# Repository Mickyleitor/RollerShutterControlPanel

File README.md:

# Roller Shutter Control Panel

Embedded wall panel for motorized shutters over radio; with LCD; buttons; Wi-Fi via ESP8266; clock;
and temperature. Open hardware with 3D-printed parts; off-the-shelf modules; and a PCB using an
ATMega328P plus ESP8266.

## Motivation and origins

Built to stop sunrise from waking me early; first a simple wall controller; then my 2020 Bachelor’s
thesis; now an open build others can replicate; learn from; and adapt. Also a testbed for new ideas.

## Project status; what it does today

Actively used and stable. Local controller for **three** shutters; buttons to move; LCD for time and
date; current temperature from the internet; on-device Wi-Fi setup; ESP8266 firmware updates over
the air. No cloud required.

## Current functionality

- **Three shutters**; Left; Center; Right; actions: Up; Down; Stop at any time.
- **16×2 I²C LCD**; Shutter management, clock on idle and configuration menu.
- **Current temperature**; periodic OpenWeatherMap request; hides value when unavailable.
- **On-device Wi-Fi setup**; scan networks; choose SSID; enable or disable Wi-Fi and OTA;
- **Auto reconnect**; for both wifi attemps and weather requests.
- **Time and timezone editor**; set time and timezone.
- **OTA updates** for the ESP8266 using ArduinoOTA; handled in the background.
- **Buzzer feedback**; adjustable volume; enable or disable; accept and error tones.
- **Debug pages**; soft reset counter; current SSID with link status; device IP.

## Repository layout

```
Docs/                     Documents
├─ Figures/               Diagrams, schematics, screenshots
├─ Files/                 Raw docs (.docx, .pdf, etc.)
└─ Photos/                Prototyping photos

Firmware_Arduino/         Arduino MCU source
Firmware_ESP8266/         ESP8266 source
Firmware_Processing_HCI/  Processing-IDE files

PCB_Design/               KiCAD board files
├─ Libraries/             Custom symbols
└─ Modules/               Footprints & 3D models

3D_Design/                Panel case models
```

## Tools

Free or evaluation to avoid licensing issues:  
• KiCAD; Arduino IDE; Google SketchUp (free); GIMP; Cameo Systems Modeler (evaluation);  
  draw.io (online); VSCode.

## License

CERN Open Hardware Licence.

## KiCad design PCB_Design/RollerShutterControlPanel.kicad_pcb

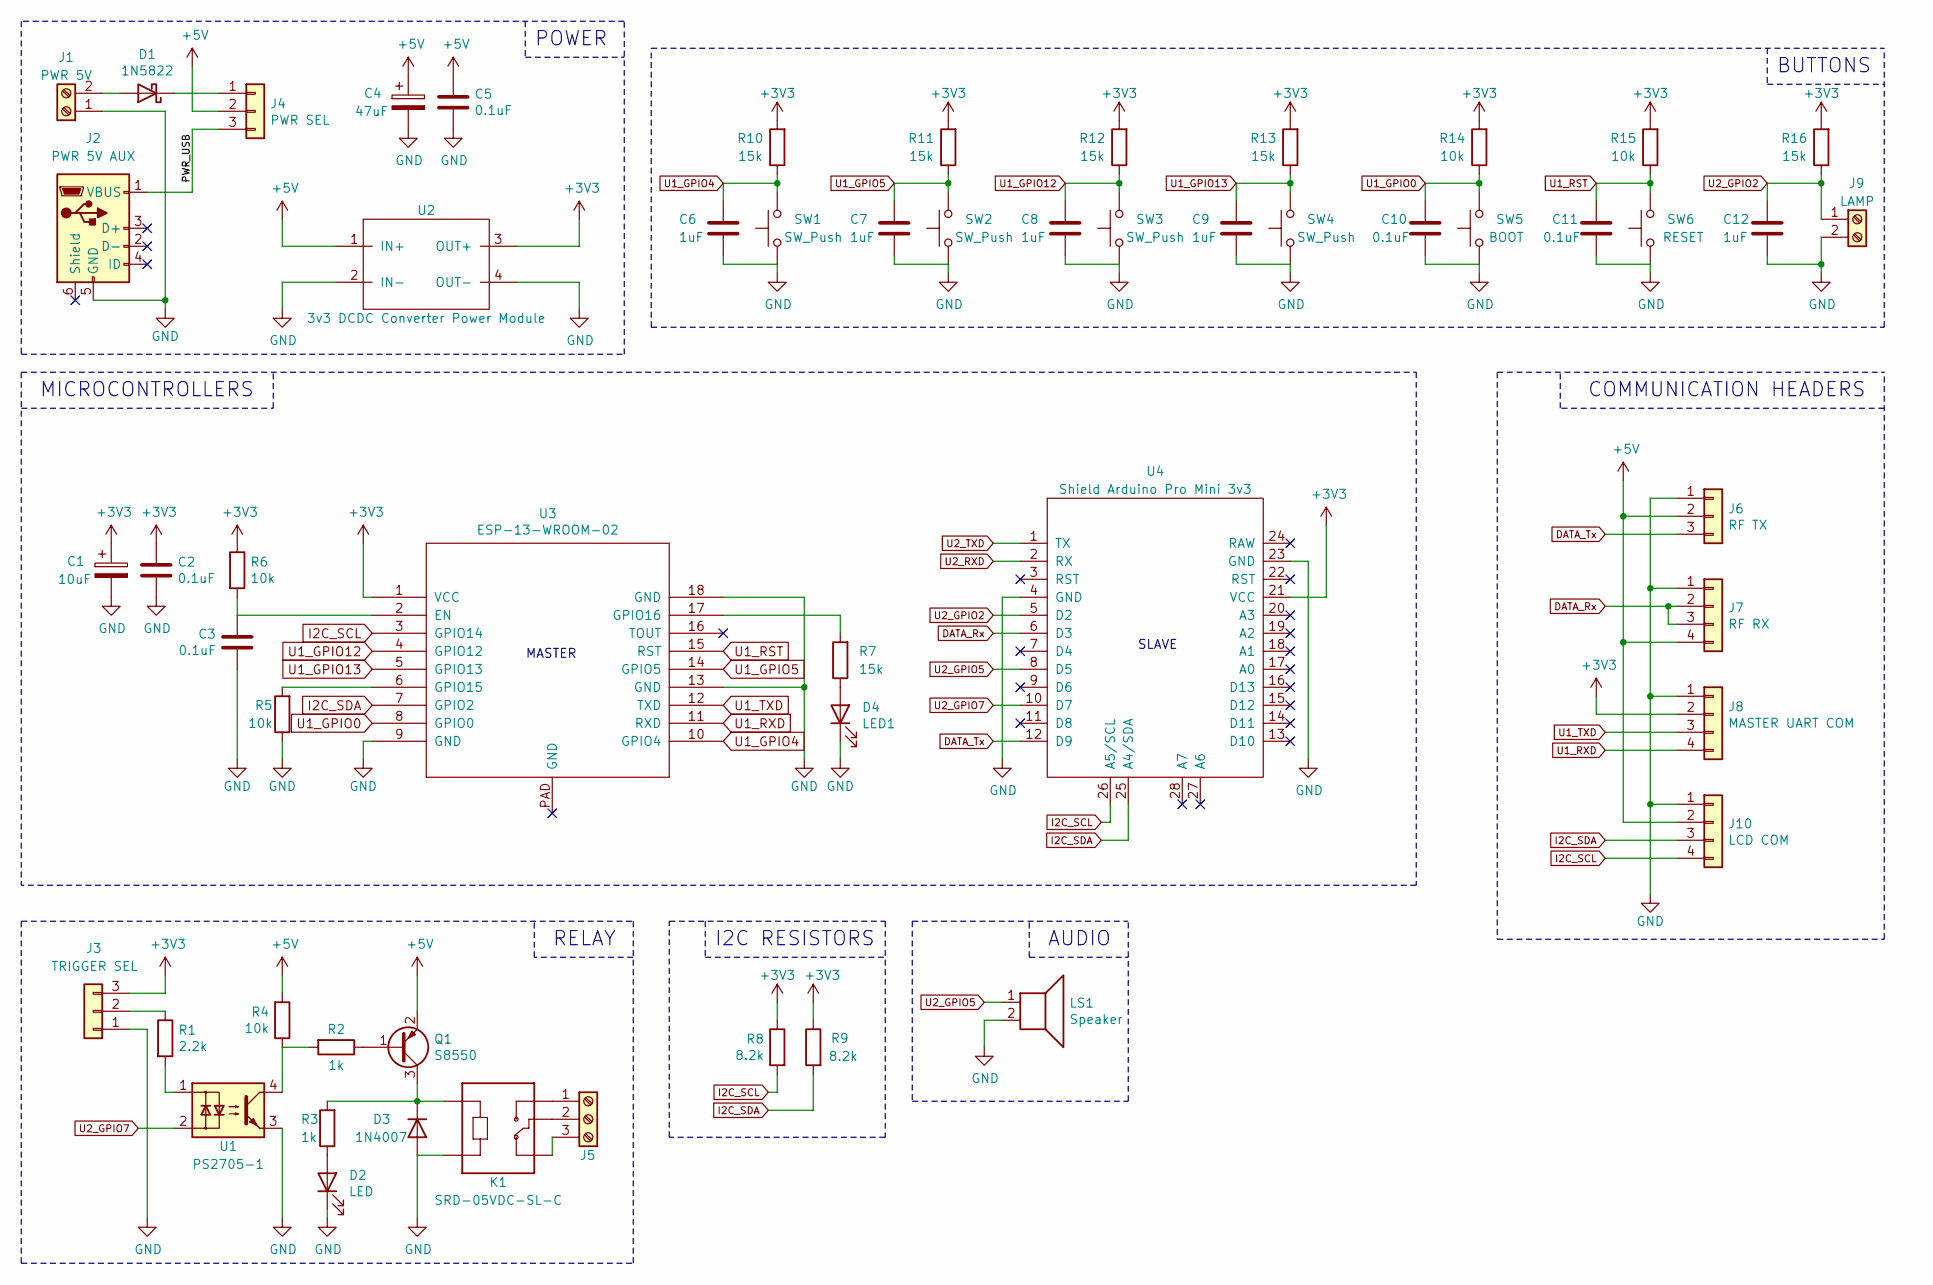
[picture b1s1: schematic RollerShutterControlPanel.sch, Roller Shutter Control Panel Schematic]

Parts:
C1: 10uF; CP_Radial_D4.0mm_P2.00mm
C2, C3, C5, C10, C11: 0.1uF; C_1206_3216Metric_Pad1.42x1.75mm_HandSolder
C4: 47uF; CP_Radial_D4.0mm_P2.00mm
C6, C7, C8, C9, C12: 1uF; C_1206_3216Metric_Pad1.42x1.75mm_HandSolder
D1: 1N5822; D_DO-201AD_P5.08mm_Vertical_KathodeUp
D2: LED; LED_D3.0mm
D3: 1N4007; D_DO-41_SOD81_P10.16mm_Horizontal
D4: LED1; LED_D3.0mm
J1: PWR 5V; PHOENIX_1935161
J2: PWR 5V AUX; USB_Mini-B_Lumberg_2486_01_Horizontal
J3: TRIGGER SEL; PinHeader_1x03_P2.54mm_Vertical
J4: PWR SEL; PinHeader_1x03_P2.54mm_Vertical
J5: Screw_Terminal_01x03; ScrewTerminal_01X03_5mm
J6: RF TX; PinSocket_1x03_P2.54mm_Vertical
J7: RF RX; PinSocket_1x04_P2.54mm_Vertical
J8: MASTER UART COM; PinHeader_1x04_P2.54mm_Vertical
J9: LAMP; PHOENIX_1935161
J10: LCD COM; PinSocket_1x04_P2.54mm_Vertical
K1: SRD-05VDC-SL-C; RELAY_SRD-05VDC-SL-C
LS1: Speaker; Buzzer_TDK_PS1240P02BT_D12.2mm_H6.5mm
Q1: S8550; SOT-23_S8550
R1: 2.2k; R_Axial_DIN0204_L3.6mm_D1.6mm_P5.08mm_Horizontal
R2, R3: 1k; R_Axial_DIN0204_L3.6mm_D1.6mm_P5.08mm_Horizontal
R4, R5, R6, R14, R15: 10k; R_Axial_DIN0204_L3.6mm_D1.6mm_P5.08mm_Horizontal
R7, R10, R11, R12, R13, R16: 15k; R_Axial_DIN0204_L3.6mm_D1.6mm_P5.08mm_Horizontal
R8, R9: 8.2k; R_Axial_DIN0204_L3.6mm_D1.6mm_P5.08mm_Horizontal
SW1, SW2, SW3, SW4: SW_Push; SW_Push_1P1T_NO_6x6mm_H5mm
SW5: BOOT; SW_Push_1P1T_NO_6x6mm_H5mm
SW6: RESET; SW_Push_1P1T_NO_6x6mm_H5mm
U1: PS2705-1; PS2705-1-F3
U2: 3v3 DCDC Converter Power Module; DCDC_3v3_PowerModule
U3: ESP-13-WROOM-02
U4: Shield Arduino Pro Mini 3v3; Socket_Strip_Arduino_MiniPro

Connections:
+3V3: C1.1, C2.1, J3.3, J8.2, R6.1, R8.1, R9.1, R10.2, R11.2, R12.2, R13.2, R14.2, R15.2, R16.2, U2.3 (OUT+), U3.1 (VCC), U4.21 (VCC)
+5V: C4.1, C5.1, J4.2, J6.2, J7.4, J10.2, Q1.2 (E), R4.2, U2.1 (IN+)
/PWR_USB: J2.1 (VBUS), J4.3
DATA_Rx: J7.2, J7.3, U4.6 (D3)
DATA_Tx: J6.3, U4.12 (D9)
GND: C1.2, C2.2, C3.2, C4.2, C5.2, C6.1, C7.1, C8.1, C9.1, C10.1, C11.1, C12.1, D2.1 (K), D3.2 (A), D4.1 (K), J1.1, J2.5 (GND), J3.1, J6.1, J7.1, J8.1, J9.2, J10.1, K1.A2, LS1.2, R5.1, SW1.1, SW2.1, SW3.1, SW4.1, SW5.1, SW6.1, U1.3, U2.2 (IN-), U2.4 (OUT-), U3.9 (GND), U3.13 (GND), U3.18 (GND), U4.4 (GND), U4.23 (GND)
I2C_SCL: J10.4, R8.2, U3.3 (GPIO14), U4.26 (A5/SCL)
I2C_SDA: J10.3, R9.2, U3.7 (GPIO2), U4.25 (A4/SDA)
unnamed: C3.1, R6.2, U3.2 (EN)
unnamed: D1.1 (K), J4.1
unnamed: D1.2 (A), J1.2
unnamed: D2.2 (A), R3.1
unnamed: D3.1 (K), K1.A1, Q1.3 (C), R3.2
unnamed: D4.2 (A), R7.1
unnamed: J3.2, R1.1
unnamed: J5.1, K1.NO
unnamed: J5.2, K1.COM
unnamed: J5.3, K1.NC
unnamed: Q1.1 (B), R2.1
unnamed: R1.2, U1.1
unnamed: R2.2, R4.1, U1.4
unnamed: R5.2, U3.6 (GPIO15)
unnamed: R7.2, U3.17 (GPIO16)
U1_GPIO0: C10.2, R14.1, SW5.2, U3.8 (GPIO0)
U1_GPIO4: C6.2, R10.1, SW1.2, U3.10 (GPIO4)
U1_GPIO5: C7.2, R11.1, SW2.2, U3.14 (GPIO5)
U1_GPIO12: C8.2, R12.1, SW3.2, U3.4 (GPIO12)
U1_GPIO13: C9.2, R13.1, SW4.2, U3.5 (GPIO13)
U1_RST: C11.2, R15.1, SW6.2, U3.15 (RST)
U1_RXD: J8.4, U3.11 (RXD)
U1_TXD: J8.3, U3.12 (TXD)
U2_GPIO2: C12.2, J9.1, R16.1, U4.5 (D2)
U2_GPIO5: LS1.1, U4.8 (D5)
U2_GPIO7: U1.2, U4.10 (D7)
U2_RXD: U4.2 (RX)
U2_TXD: U4.1 (TX)

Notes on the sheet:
I2C RESISTORS
AUDIO
SLAVE
MASTER
COMMUNICATION HEADERS
RELAY
MICROCONTROLLERS
BUTTONS
POWER

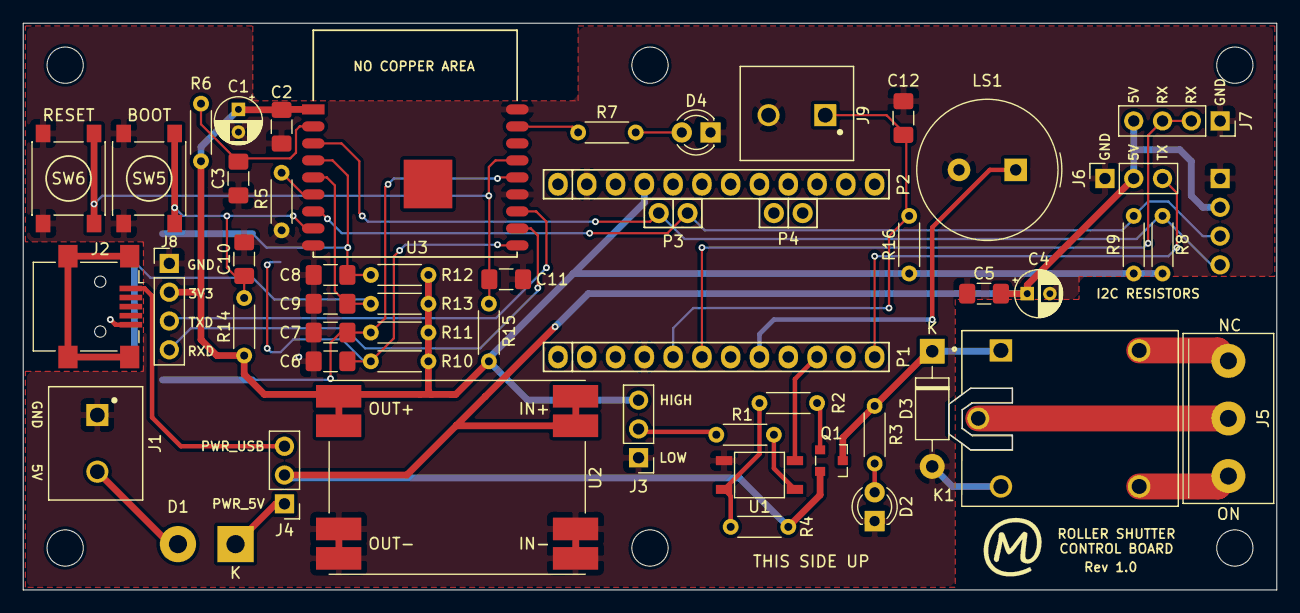
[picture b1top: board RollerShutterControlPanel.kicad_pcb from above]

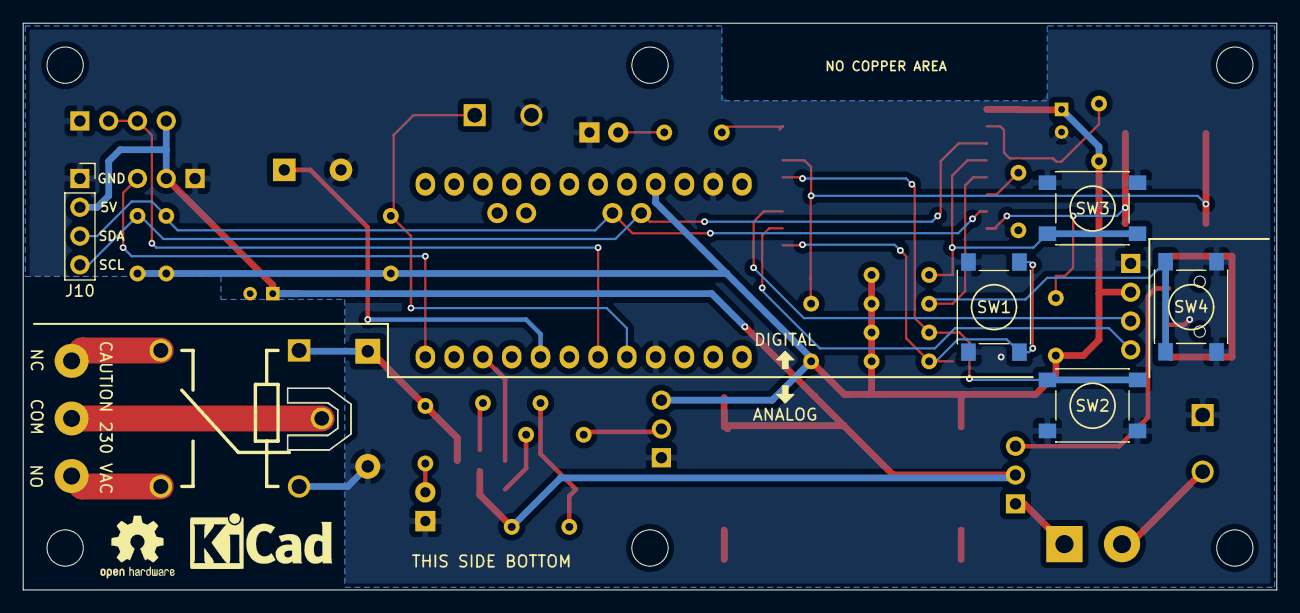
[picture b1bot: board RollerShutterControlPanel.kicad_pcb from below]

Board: 2 copper layers, 110.6 x 50.0 mm, 56 parts (6 on the bottom side), 34 nets.

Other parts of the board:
Carcasa: Carcasa

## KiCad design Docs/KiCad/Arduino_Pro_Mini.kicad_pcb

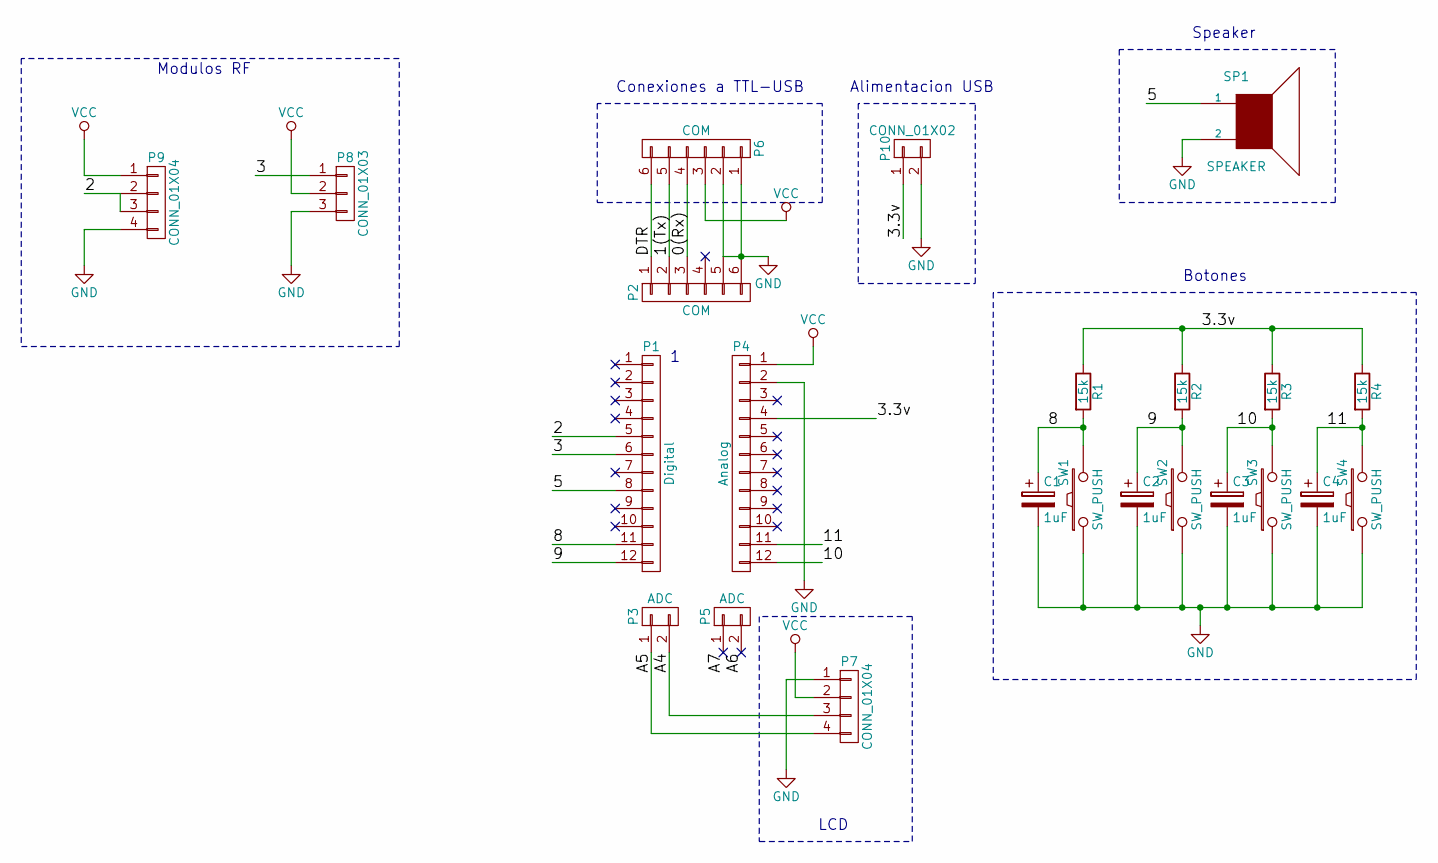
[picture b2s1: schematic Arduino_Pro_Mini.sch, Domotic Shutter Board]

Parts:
C1, C2, C3, C4: 1uF; CP_Radial_D4.0mm_P2.00mm
P1: Digital; Socket_Strip_Straight_1x12_Pitch2.54mm
P2: COM; Socket_Strip_Straight_1x06_Pitch2.54mm
P3, P5: ADC; Socket_Strip_Straight_1x02_Pitch2.54mm
P4: Analog; Socket_Strip_Straight_1x12_Pitch2.54mm
P6: COM; Pin_Header_Straight_1x06_Pitch2.54mm
P7, P9: CONN_01X04; Socket_Strip_Straight_1x04_Pitch2.54mm
P8: CONN_01X03; Socket_Strip_Straight_1x03_Pitch2.54mm
P10: CONN_01X02; Pin_Header_Straight_1x02_Pitch2.54mm
R1, R2, R3, R4: 15k; R_Axial_DIN0207_L6.3mm_D2.5mm_P10.16mm_Horizontal
SP1: SPEAKER; Buzzer_12x9.5RM7.6
SW1, SW2, SW3, SW4: SW_PUSH; SW_PUSH_6mm

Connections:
/0(Rx): P2.3, P6.4
/1(Tx): P2.2, P6.5
/2: P1.5, P9.2, P9.3
/3: P1.6, P8.1
/3.3v: P4.4, P10.1, R1.1, R2.1, R3.1, R4.1
/5: P1.8, SP1.1
/8: C1.1, P1.11, R1.2, SW1.2
/9: C2.1, P1.12, R2.2, SW2.2
/10: C3.1, P4.12, R3.2, SW3.2
/11: C4.1, P4.11, R4.2, SW4.2
/A4: P3.2, P7.3
/A5: P3.1, P7.4
/A6: P5.2
/A7: P5.1
/DTR: P2.1, P6.6
GND: C1.2, C2.2, C3.2, C4.2, P2.5, P2.6, P4.2, P6.1, P6.2, P7.1, P8.3, P9.4, P10.2, SP1.2, SW1.1, SW2.1, SW3.1, SW4.1
VCC: P4.1, P6.3, P7.2, P8.2, P9.1

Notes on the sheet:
Modulos RF
LCD
Conexiones a TTL-USB
Speaker
Botones
Alimentacion USB

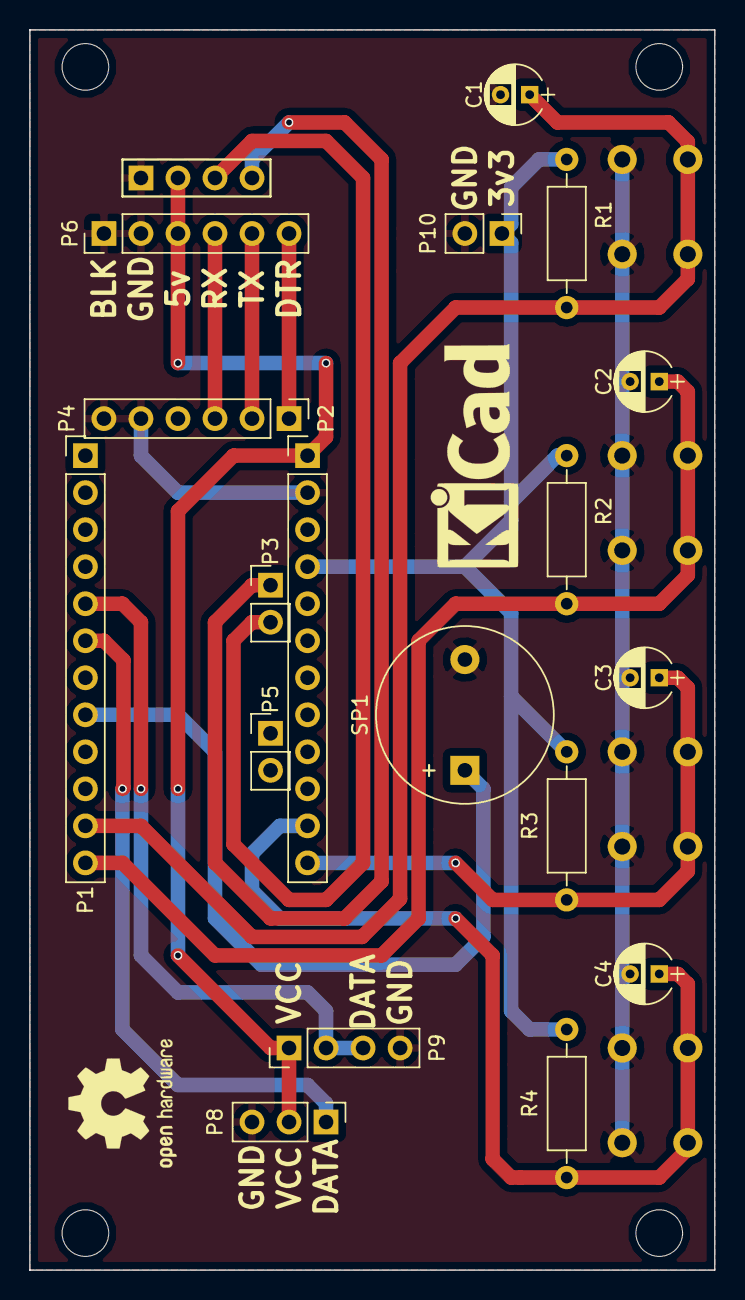
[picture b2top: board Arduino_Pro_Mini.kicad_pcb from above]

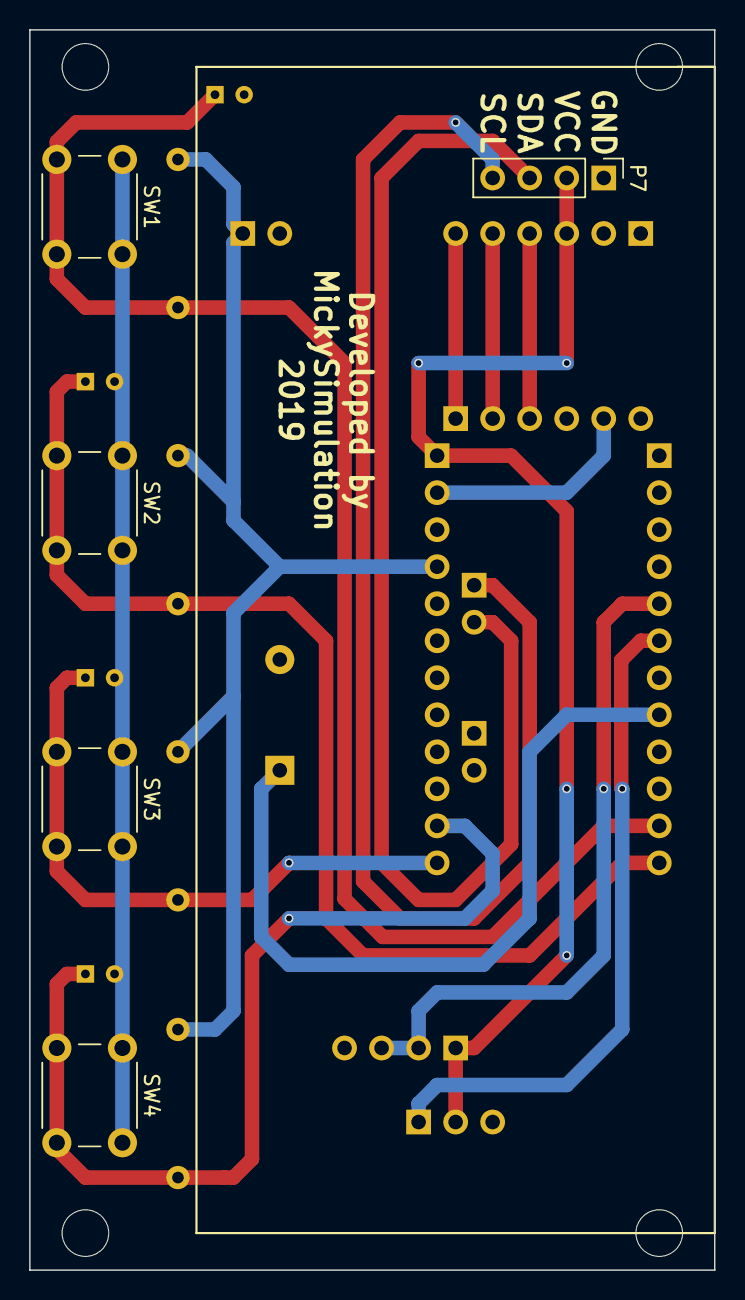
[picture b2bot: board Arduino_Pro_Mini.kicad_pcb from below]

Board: 2 copper layers, 47.0 x 85.1 mm, 23 parts (5 on the bottom side), 15 nets.

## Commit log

2018-09-19 Initial upload
2018-09-19 Muecas tornillos y forma de la base
2018-09-20 Holes to support the base for connectors
2018-10-09 Pieza para USB y FTDI
2018-10-10 Modelo 3D embellecedor y soporte completado
2018-10-10 Completed 3D parts
2018-10-10 Exported 3D Parts to STL format
2018-10-10 ignore .skb files
2018-10-22 Changed readme
2019-03-27 Reseted software and updated images
2019-04-04 KiCAD project
2019-04-06 PCB terminada
2019-04-07 Frontal caja 3D
2019-04-08 Reducida tamaño PCB
2019-04-08 Panel USB
2019-04-08 Readme con imagenes
2019-04-09 Soporte 3D para PCB
2019-04-26 Added Domotic Shutter FSM
2019-04-26 huecos tornillos
2019-04-26 FSM folder
2019-04-26 Edited readme
2019-05-11 README actualizado
2019-05-16 Wireframe image
2019-05-18 Video resources
2019-05-18 Video resoures edited
2019-05-19 New resources on the way!
2019-05-21 Real PCD images
2019-05-22 Rotated image
2019-07-03 Brass Inserts holes
2019-09-01 basic defines
2019-09-01 dependecies
2019-09-01 Deleted dependecies
2019-09-07 Lcd messages
2019-09-13 More functions
2019-11-20 File structure
2020-03-23 CAMEO files
2020-03-23 CAMEO last file
2020-03-25 New requirements and organized layout
2020-04-07 Introduced timeLib and New requirements
2020-04-11 Working libraries
    Working LCD, wifi, Time, NTPTime, get weather info from openweather, hide auth info.
2020-04-11 TimeAlarm commented
2020-04-11 Ignore auth information
2020-04-20 Schematic updated and code
    * Code is updated with a new finite state machine for LCD messages.
    * SoftwareSerial updated to support my own ISR
    * Buttons interrupts added
    * New schematic using the Relay approach
    * Kicad Own Libraries added
2020-04-21 3V3 Power Module Library
    Added ESP and LCD connectors to schematic
2020-04-24 Changed to radio approach
2020-04-28 Changed architecture to ESP8266 as master
    See documentation
2020-06-16 lcd stm Diagram
    * lcd diagram nearly completed
    * Added new 3d library for arduino pro mini
2020-06-16 Comms from master to slave test
2020-08-08 Slave main functions completed
    - Roller shutter working
    - Buzzer working
2020-08-10 Navigation Menu though Manager and Mode
    - Added a function to check slave connection.
    - The system now implement an fsm of the RollerShutter.
    - yield() function added at the end of loops to perform RTOS tasks.
    - Added and tested sucessfully sending command to rollerShutter via sendRollerCommand.
    - Navigation Arrows completed though RollerManager and Modes (lack secondary functions) and the functions to perform the real action.
    - Activity function for procesoDesactivarTarea/procesoActivarTarea completed.
2020-08-12 Added Jobmod, switch commands, suncalcs and getweather
    - Added Job mode
    - Added switch commands in slave and master
    - Added suncalculation library to get sun azimuth
    - Added a function getweatherData to get online data of the current weather
    - The system now store UTC time.
2020-08-14 More meaningfull var names
    The scheduled data now is stored in [12] {[2][31]} struct. (Todo : use the memory more efficiently)
2020-08-14 struct to two dimensional array var for scheduledData
2020-08-27 EEPROM storing and UI completed
    Also a sketch in Processing was developed to test the UCD principles for the UI.
2020-08-27 Menu sleep to a new main menu
2020-08-27 Italiano
2020-08-27 Flash when job mode
2020-08-29 Updated 3D model to Crossed layout
2020-08-29 Changed text labels
2020-09-02 Added buzzer and 3d model updated
2020-09-16 Schematic cleanup and new 3d models
    3d models for S8550 and PS2701
2020-09-17 Unified libraries to one
2020-09-17 Pins slaved fixed and Serial messages debug
2020-09-17 Changed folder structure
2020-09-21 Updated 3D models and schematic
    Arduino symbol changed in schematic. The UART connector is no longer displayed and I can be accessed externaly.
    New 3D models for 400mhz modules, buzzer and conectors.
2020-09-26 Changed to SMD pushbutton
2020-09-27 R and C added for buttons
2020-10-02 Positioned all footprints
2020-10-02 New design rules
2020-10-03 Traced tracks
2020-10-05 Archived footprints
2020-10-05 Ready to production
2020-10-09 Renamed files
2020-10-14 Added org files in readme
2020-10-19 Spanish
2020-10-20 updated from master
2020-10-20 Added text to Processing
2020-10-21 HCI UX images
2020-10-26 MBSE
2020-11-15 Specifications
2020-11-15 New randomized Layout in Processing
2020-11-16 Added criticalData only tfg branch
    Pushed criticalData.h to allow the compilation by the jury reviewing this project
2021-07-25 Definiciones de texto para castellano
2023-07-27 Isolate radioProtocol low level functions
2023-07-30 radioProtocolo module to a subfolder
2023-08-09 radioProtocol low level changed to use bytes instead of bits in arguments
2023-08-24 Uses arduino CLI and github-action for compile
2023-08-24 Test compile-arduino-sketch on github actions
2023-08-24 add library to github-action
2023-08-24 Add criticalData to make Github-actions work
2023-08-28 Better error handling for lcd and wifi sta
2023-08-29 First isolation of wifi functions and update github actions to also compile ESP8266 firmware
2023-08-29 additional urls is needed for esp8266 in actions
2023-08-29 call of overloaded 'abs(long unsigned int)' is ambiguous in abs()
2023-08-29 Better handling of EEPROM functions
2023-08-30 Store openweathermap data in EEPROM
2023-09-04 Opens an AP if STA isn't available
2023-09-05 Bump actions/checkout from 3 to 4
    Bumps [actions/checkout](https://github.com/actions/checkout) from 3 to 4.
    - [Release notes](https://github.com/actions/checkout/releases)
    - [Changelog](https://github.com/actions/checkout/blob/main/CHANGELOG.md)
    - [Commits](https://github.com/actions/checkout/compare/v3...v4)
    ---
    updated-dependencies:
2023-09-06 Creation of AP if STA isn't available (AP features not implemented yet), better isolation of buttons API and a proper enter/idling/wakeup procedures.
2023-09-06 Remove dependabot
2023-09-07 Wrong state change. Moved more items to esp8266_utils
2023-09-07 Slave functions moved to Slave_Utils
2023-09-10 Added Roller Shutter Control Panel Protocol (RSCP) for i2c communication stack protocol
2023-09-11 Moved rscp library to a submodule. Working cpuquery
2023-09-11 update submodules on github actions
2023-09-12 LowPower in AVR and proper button interrupts.
2023-09-13 Task is now received and buffered locally
2023-09-15 Fully working RSCP protocol (a few very basic cmd implemented) and doxygen format
2023-09-17 Update rscp submodule
2023-09-17 Better enum for better readiness
2023-09-17 lcd object separated on its own file
2023-09-18 Added a readme with some ideas
2023-09-19 stored data now have a proper settings structure
2023-09-21 Heavy refactor. Isolated (or almost) all lcd related functions and changed system state transitions. Better enums
2023-09-23 Added menu wifi info to lcd
2023-09-23 Better display of lcd initial wifi configuration
2024-05-30 Clang format
2025-07-14 Change on UI reqs for simpler panel
2025-07-20 Roadmap
2025-07-20 Job action removed
2025-07-20 Better readme
2025-07-20 Rename with _ISR()
2025-07-20 Removed sleep mode and actions
2025-07-20 Removed unnecesary settings
2025-07-20 Remove AP mode
2025-07-21 Update to have PlatformIO enviroment
2025-07-21 Removed abusive use of ticker. Screen is now updated in main loop. Return to default menu after waking up if menu are not a shutter when there is a button timeout.
2025-07-22 Better lcd functions that make code easier in main
2025-07-23 Add menu config
2025-07-23 fix compilation
2025-07-23 Added menu to change hour and date
2025-07-25 Redesigned rtc time
2025-07-25 keep adjust level if releasing button for less than 2 sconds when changing the time
2025-07-25 sound redesign and buttons ticker removed.
2025-07-26 Add menu for changing volume
2025-07-27 Menu for timezone
2025-07-30 New way to store persistent variables.
2025-07-31 Flash which digit is changing when editing time
2025-07-31 Changed to a way much simpler way to update time.
2025-07-31 More API functions! I'm having a good time.. (really).
2025-07-31 Reset counter menu
2025-07-31 Safer writes to EEPROM.
2025-07-31 Clean up headers
2025-08-01 Wifi password menu
2025-08-05 Wifi ssid
2025-08-06 Safer eeprom scheduled writes
2025-08-06 Some fixes given by copilot
2025-08-06 better defines
2025-08-06 Feature menu wifi ssid (#12)
    * Wifi ssid
    * Safer eeprom scheduled writes
    * Some fixes given by copilot
    * better defines
2025-08-06 better encapsulation of pending configuration in lcd
2025-08-08 Refactor WiFi settings and update handling; add able to disable/enable ble and display wifi/weater indication icon in screen
2025-08-08 Feature menu wifi ssid (#13)
    * Wifi ssid
    * Safer eeprom scheduled writes
    * Some fixes given by copilot
    * better defines
    * better encapsulation of pending configuration in lcd
    * Refactor WiFi settings and update handling; add able to disable/enable ble and display wifi/weater indication icon in screen
2025-08-08 OTA!!!!
2025-08-08 First release for real-world-ready use.
2025-08-10 Fixed a bug with long real radio frame. Handle rscp errors.
2025-08-11 Add platformIO in all projects. Modify actions to compile with pio
2025-08-11 Spanish to english comments
2025-08-11 Add platformIO in all projects. Modify actions to compile with pio (#14)
    * Add platformIO in all projects. Modify actions to compile with pio
    * Spanish to english comments
2025-08-31 New 3D printed part. Installed in site.
2025-09-22 Feature update to platformio (#15)
    * Add platformIO in all projects. Modify actions to compile with pio
    * Spanish to english comments

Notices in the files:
PCB_Design/RollerShutterControlPanel.kicad_pcb:
Released under CERN Open Hardware Licence v2
